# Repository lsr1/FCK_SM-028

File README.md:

# SM-028_v1.3-to-ESP32-PICO-D4
passive pcb adapter-plate (drop-in replacement) for SM-028_v1.3 Wi-Fi Module to a ESP32-PICO-D4

## Executive Summary
* This projects provides a drop-in replacement for a "[TROLINK SM-028_V1.3 BL602L20](https://www.elektroda.com/rtvforum/topic3945435.html)". 
* This project consists of a KiCad project that gives you the Gerber files to order a PCB (e.g. at [JLCPCB](https://cart.jlcpcb.com)) onto which one ESP32-PICO-D4, three capacitors, one antenna and one resistor are soldered. <br>
* For the impatient: Go to [Installation](#Installation). 
* I did this for [these E27 lamp holders](https://www.aliexpress.com/w/wholesale-Wifi-Smart-Light-Bulbs-Adapter-Mini-e27-Lamp-Holde.html?spm=a2g0o.productlist.search.0).

## Picture

## Sidenotes
This is yet another quick hack project and thus neither very polished nor professional - plz use at your own risk. The readme is long (as usual), as I want to document the journey. </br>
Despite the verbosity of the readme, it assumes that you know how to solder micro lead frame (MLF) packages and some basic electronics. Some things here are weirdly specific, while some are infuriatingly generic (assuming a lot of knowhow). 

## Preamble (Why)
Some years ago (in the dawn of IoT), Sonoff manufactured a 'smart E27 lampholder' called Slampher (that had an esp8266 inside). I bought some, b/c my parents wanted to switch lights on and off to a given schedule when they were out, and Tasmota provides a nice way to do that w/o a central control station. Unfortunately, the Slampher was discontinued (who still needs this if you can buy an E27 bulb with an ESP inside). So I bought what I thought was yet another WiFi enabled E27 holder on Ali (see above) - just to find out that there was no ESP chip inside. The WiFi module proved to be not hackable :-(. 

Long story short: Once again I compared the voltages and signal pins - turns out these fit to an ESP! [So here we go again](https://www.youtube.com/watch?v=dTAAsCNK7RA) I guess. 

## Pin-mapping
|row #| SM-028_v1.3 (pad)| SM-028_v1.3 (usage in E27) | ESP32 (pin)|
--- | --- | --- | ---
|1|L (front)| n/a |GPIO25 (14)|
|2|A (front) |GND| GPIO26 (15)|
|3|B (front) |relais| GPIO27 (16)|
|4|G (front)|button|GPIO14 (17)|
|5|R (front) |n/a|GPIO19 (38)|
|6|3V3 (back)|VCC|VCC (1 and others)|
|7|GND (back) |GND|GND (49 pad)|
|8|22 (back) |blue LED|GPIO22 (39)|
|9|17 (back)|n/a|GPIO4 (24)|
|10|C (back)|n/a|GPIO9 (28)|
|11|W (back)|n/a|GPIO23 (36)|

## Design Decisions
* Size must not be larger than the SM-028_v1.3 module (so that it is in fact a drop in replacement).
* Drop-in replacement, thus all pins must retain the same position and function
* Utilize as many ESP pins as possible (no empty pads on module).
* Have the least amount of components possible (I hate placing and soldering chicken feed). 
* Price does not matter (favour integration over lots of components).
* Have test-pads for soldering on leads for GND, VCC, GPIO0, RX, TX for flashing. 
* All components on one side for easier reflow soldering.
* Have a component antenna (not an etched one; I stole the antenna-idea from the [Picoclick-C3](https://github.com/makermoekoe/Picoclick-C3)). 
* I chose 0805 b/c there was enough space, the antennae was large anyway, and b/c it's easier to solder. Sue me.

## BOM (for 1 module; each part needed once)
* PCB (see [Installation](#Installation)).
* ESP32-PICO-D4 
* R1: 12k 0805
* C1: 0.1 μF 0805
* C3: 1 μF 0805
* C2: 10 μF 0805
* AE1: ANT3216LL00R2400A

## Installation
* Go to [JLCPCB](https://cart.jlcpcb.com/quote) and upload the [gerbers.zip](gerber/FCK_SM-028_V1.3-gerbers.zip). Sidenote: I'm neither sponsored nor do I endorse them specifically, I just find them convenient. <b>Make sure you select the correct PCB thickness (0.8 mm).</b> I also set "Remove Order Number" to "Specify a location" (layout contains a field for this). No other special settings. I also purchased a stencil (YMMV). 
* Get the parts. 
* Reflow the components (I use [this](https://eu.mouser.com/ProductDetail/Chip-Quik/SMDLTLFP?qs=aBQo9TmGG4V1bvEQuyksHg%3D%3D)).  
* Solder jumper wires to the pads on the back, and flash your desired image (note: the ESP32 might need a boot-loader flashed too).

## Software
* I use this [ESPHome config](ESPhome/esp32test.yaml) config.

## License and Legalese
* May be (re)used for personal/private use only and not sold/licensed for commercial or financial gain. This non-standard license should make it impossible and really difficult for commercial enterprises to profit from my work (pay people to design this!), but enable the hobbyist/enthusiast to work with it. 
* If I have inadverently (re-)used your work without either properly attributing it or something, please let me know - I'd be happy to correct this.

## Donations
Yes please.

## Feedback
Also yes please! (I hope I figure out how this whole pull-request thing works...)

## Shoutout ...
* ... to [CCC](https://www.ccc.de) and [CCCZH](https://www.ccczh.ch/)!
* ... to all FOSS contributors that helped making SW that enabled me to do this. Nanos gigantium humeris insidentes.

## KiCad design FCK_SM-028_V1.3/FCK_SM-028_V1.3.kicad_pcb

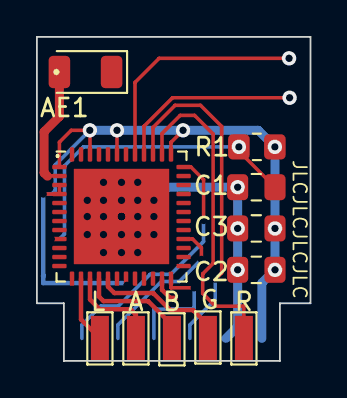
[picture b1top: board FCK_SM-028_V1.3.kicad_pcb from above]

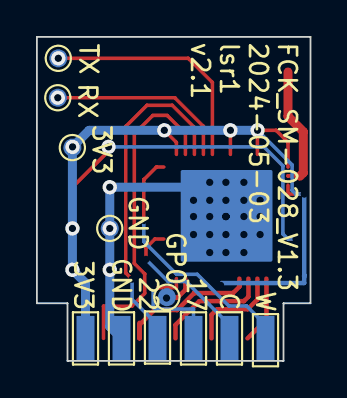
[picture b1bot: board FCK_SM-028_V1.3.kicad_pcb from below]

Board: 2 copper layers, 15.2 x 18.0 mm, 22 parts (11 on the bottom side), 15 nets.

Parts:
3V3: inVCC; TestPoint_Pad_D1.0mm
3V3#2: ex3V3; TestPoint_Pad_1.0x2.5mm
17: ex17; TestPoint_Pad_1.0x2.5mm
22: ex22; TestPoint_Pad_1.0x2.5mm
A: exA; TestPoint_Pad_1.0x2.5mm
AE1: Antenna_Chip; Johanson_2450AT18x100
B: exB; TestPoint_Pad_1.0x2.5mm
C: exC; TestPoint_Pad_1.0x2.5mm
C1: 0.1uF; C_0805_2012Metric_Pad1.18x1.45mm_HandSolder
C2: 10uF; C_0805_2012Metric_Pad1.18x1.45mm_HandSolder
C3: 1uF; C_0805_2012Metric_Pad1.18x1.45mm_HandSolder
FCK_SM-028_V1.3: ESP32-PICO-D4; QFN-48-1EP_7x7mm_P0.5mm_EP5.3x5.3mm
G: exG; TestPoint_Pad_1.0x2.5mm
GND: inGND; TestPoint_Pad_D1.0mm
GND#2: GND; TestPoint_Pad_1.0x2.5mm
GP0: inD0; TestPoint_Pad_D1.0mm
L: exL; TestPoint_Pad_1.0x2.5mm
R: exR; TestPoint_Pad_1.0x2.5mm
R1: 12K; R_0805_2012Metric_Pad1.20x1.40mm_HandSolder
RX: inRX; TestPoint_Pad_D1.0mm
TX: inTX; TestPoint_Pad_D1.0mm
W: exW; TestPoint_Pad_1.0x2.5mm

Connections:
GND: C1.1, C2.1, C3.2, FCK_SM-028_V1.3.49 (GND), GND.1, GND#2.1
unnamed: AE1.2 (PCB_Trace), FCK_SM-028_V1.3.2 (LNA_IN)
unnamed: C1.2, FCK_SM-028_V1.3.9 (EN), R1.1
unnamed: FCK_SM-028_V1.3.41 (U0TXD/IO1), TX.1
unnamed: FCK_SM-028_V1.3.40 (U0RXD/IO3), RX.1
VCC: 3V3.1, 3V3#2.1, C2.2, C3.1, FCK_SM-028_V1.3.1 (VDDA), FCK_SM-028_V1.3.3 (VDDA3P3), FCK_SM-028_V1.3.4 (VDDA3P3), FCK_SM-028_V1.3.19 (VDD3P3_RTC), FCK_SM-028_V1.3.37 (VDD3P3_CPU), FCK_SM-028_V1.3.43 (VDDA), FCK_SM-028_V1.3.46 (VDDA), R1.2
ex17: 17.1, FCK_SM-028_V1.3.24 (IO4)
ex22: 22.1, FCK_SM-028_V1.3.39 (IO22)
exA: A.1, FCK_SM-028_V1.3.15 (IO26)
exB: B.1, FCK_SM-028_V1.3.16 (IO27)
exC: C.1, FCK_SM-028_V1.3.28 (SD2/IO9)
exG: FCK_SM-028_V1.3.17 (IO14), G.1
exL: FCK_SM-028_V1.3.14 (IO25), L.1
exR: FCK_SM-028_V1.3.38 (IO19), R.1
exW: FCK_SM-028_V1.3.36 (IO23), W.1

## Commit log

2024-06-21 fixed pic
2024-06-21 fixed some typos in readme
